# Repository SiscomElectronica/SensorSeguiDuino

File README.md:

# SensorSeguiDuino

Sensor optico para el un seguidor de lineas

## Descripcion

El proyecto consta de 2 archivos importantes:

*Sensor.sch: Diagrama electrico del proyecto

*Sensor.brd: Archivo del diseño del circuito impreso

*cny70.lbr: Libreria del sensor CNY70

## Consideraciones

Muchos componentes fueron modificados desde su libreria, asi que puede 
marcar algunos errores con respecto a su descarga y posterior modifcacion.

Si deseas hacer modificaciones tienes que tomar en cuenta que debes agregar
la libreria: "cny70.lbr", a la carpeta lbr de donde hallas instalado eagle.

Con respecto a su fabricacion al no tener archivos (.gbr) gerber es 
necesario contactar al fabricante y proporcionarle el archivo 
Siscom_SEGUIDOR.brd para su posterior manufacturacion.

Diseñado por: [Josue Echeverria](https://www.facebook.com/josue.echeverria.583)

Team SISCOM.

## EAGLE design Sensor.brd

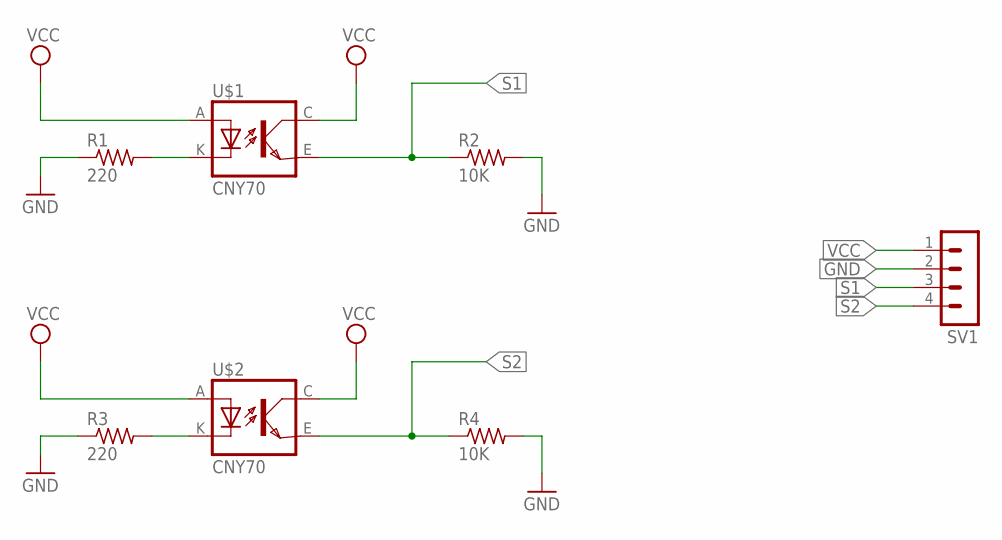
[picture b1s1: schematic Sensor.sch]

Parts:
R1, R3: 220; 0207/10
R2, R4: 10K; 0207/10
SV1: MA04-1
U$1, U$2: CNY70; 4

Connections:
GND: R1.1, R2.2, R3.1, R4.2, SV1.2
unnamed: R1.2, U$1.K (C)
unnamed: R3.2, U$2.K (C)
S1: R2.1, SV1.3, U$1.E (EMI)
S2: R4.1, SV1.4, U$2.E (EMI)
VCC: SV1.1, U$1.A, U$1.C (COL), U$2.A, U$2.C (COL)

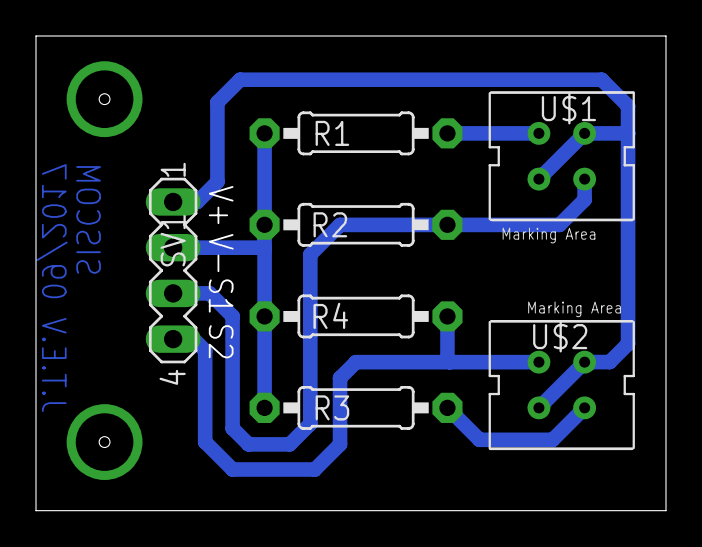
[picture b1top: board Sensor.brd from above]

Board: 2 copper layers, 35.0 x 26.4 mm, 7 parts (0 on the bottom side), 6 nets.

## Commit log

2017-09-06 Diseno de Esquematico
2017-09-06 Anexo del borrador README
2017-09-07 Version_1
2017-09-07 Actualizacion
